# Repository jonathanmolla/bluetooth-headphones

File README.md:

# Bluetooth Headphones

Custom Bluetooth headphone electronics by **Jonathan Molla**, bringing together stereo audio circuit design, PCB layout, battery charging, STM32 controller configuration, and LTspice simulation.

## Project at a glance

| Area | Implementation in this repository |
| --- | --- |
| Bluetooth audio | Microchip BM83 module in the KiCad audio schematic |
| Headphone amplifier | TI TPA6130A2, with AC-coupled analog inputs |
| Controller | STM32U031C8T6 configuration and MCU/button schematic |
| Charging | MCP73833 circuit on a separate power PCB |
| Regulation | TPS7A2030PDBVR, fixed 3.0 V regulator |
| Design tools | KiCad, STM32CubeMX, LTspice |
| Simulation scope | Simplified analog coupling and voltage-gain models |

## Explore the project

| What you want to see | Where to find it |
| --- | --- |
| **PCB layouts and editable board files** | [Main audio PCB](hardware/main/#main-audio-pcb) · [Charging and power PCB](hardware/power/#charging-and-power-pcb) |
| **Schematics** | [Audio, controller, and charging circuit diagrams](docs/schematics/) |
| **Board images** | [Main audio and power board previews](docs/images/) |
| **Circuit design and component choices** | [Architecture and design decisions](docs/design.md) |
| **STM32 configuration** | [Controller pin and peripheral configuration](firmware/) |
| **Audio simulation** | [LTspice circuit, models, and run instructions](simulation/) |
| **Component lists** | [Main audio board BOM](hardware/main/bom.csv) · [Power board BOM](hardware/power/bom.csv) |
| **Engineering checks** | [Schematic and PCB check results](docs/validation.md) |
| **Opening the design files** | [Software and setup guide](docs/getting-started.md) |
| **Design deliverables** | [Project file guide](docs/roadmap.md) |

## System architecture

```mermaid
flowchart LR
    BT[Bluetooth source] --> BM[BM83 module]
    BM --> AC[AC coupling]
    AC --> AMP[TPA6130A2 amplifier]
    AMP --> HP[Left and right headphone drivers]
    USB[USB power input] --> CHG[MCP73833 charging circuit]
    CHG <--> BAT[Single-cell battery]
    BAT --> RAIL[VBAT rail]
    RAIL --> BM
    RAIL --> AMP
    RAIL --> LDO[TPS7A20 3.0 V regulator]
    LDO --> MCU[STM32U031 controller]
    BTN[Buttons] --> MCU
    MCU -. control interfaces .-> BM
    MCU -. I2C control .-> AMP
```

This is an architectural overview. Exact connections and component values are defined by the native schematics. The main/audio board and charging/power board are separate KiCad projects.

## Engineering highlights

- Hierarchical schematic organization for audio and MCU controls.
- A separate charging and regulation PCB.
- Project-local symbols and footprints alongside the native KiCad files.
- Stereo AC-coupling analysis with parameterized input resistance, gain, and driver loads.
- STM32 pin and peripheral configuration captured in a reproducible `.ioc` file.
- Recorded KiCad electrical and design-rule checks with a structured measurement procedure.

## Repository layout

```text
hardware/
  main/          Main audio PCB, audio and controller schematics, local libraries
  power/         Charging and power PCB, schematic and local libraries
firmware/        STM32CubeMX controller configuration
simulation/      LTspice audio circuit, symbols, models and instructions
docs/
  images/        PCB layout previews
  schematics/    Browser-readable schematic exports
  checks/        Recorded KiCad design checks
```

## Author and references

Project owner: [Jonathan Molla](https://github.com/jonathanmolla).

See [references and third-party materials](docs/references.md) for component sources and [reuse information](NOTICE.md) before reusing the files.

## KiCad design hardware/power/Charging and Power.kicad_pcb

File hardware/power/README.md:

# Charging and power board

This board contains the USB power input, MCP73833 battery-charging circuit, and TPS7A2030PDBVR 3.0 V regulator.

## Charging and power PCB

**Editable board layout:** [Charging and Power.kicad_pcb](Charging%20and%20Power.kicad_pcb)

**Open the complete KiCad project:** [Charging and Power.kicad_pro](Charging%20and%20Power.kicad_pro)

**View the layout in your browser:** [Charging and power PCB preview](../../docs/images/power-board.svg)

## Schematic and component list

| File | Contents |
| --- | --- |
| [Power schematic](Charging%20and%20Power.kicad_sch) | Charging, regulation, indicators and board connections |
| [Component list](bom.csv) | Schematic references, values, footprints and datasheet links |

[View the power schematic](../../docs/schematics/power/Charging%20and%20Power.svg) · [Open the main audio board](../main/)

## Library files

`MCP73833-AMI_UN.pretty/` and `TPS7A2030PDBVR.pretty/` contain the local charger and regulator CAD assets. Keep these folders and both library tables beside the project when downloading it.

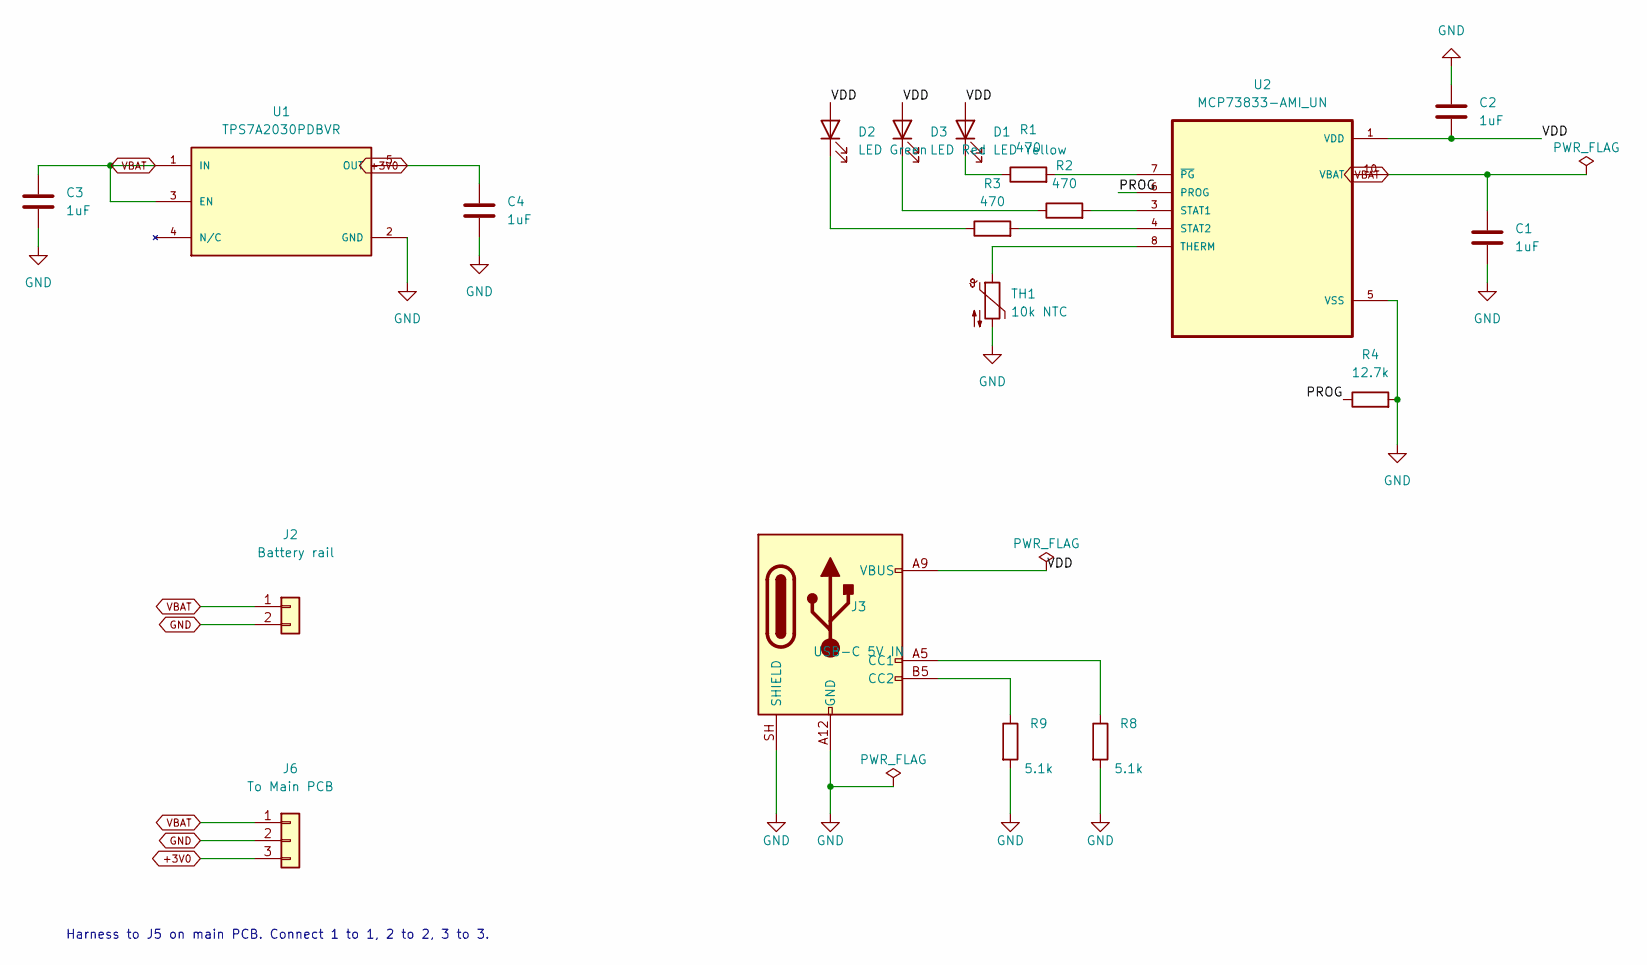
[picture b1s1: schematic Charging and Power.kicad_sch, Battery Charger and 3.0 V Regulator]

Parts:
C1, C2, C3, C4: 1uF; C_0805_2012Metric; MPN GRM219R71E105KA88D
D1: LED Yellow; LED_0805_2012Metric; MPN AP2012SYC
D2: LED Green; LED_0805_2012Metric; MPN AP2012SGC
D3: LED Red; LED_0805_2012Metric; MPN APT2012SURCK
J2: Battery rail; JST_PH_B2B-PH-K_1x02_P2.00mm_Vertical; MPN B2B-PH-K-S(LF)(SN)
J3: USB-C 5V IN; USB_C_Receptacle_GCT_USB4125-xx-x_6P_TopMnt_Horizontal; MPN USB4125-GF-A
J6: To Main PCB; JST_PH_B3B-PH-K_1x03_P2.00mm_Vertical; MPN B3B-PH-K-S(LF)(SN)
R1, R2, R3: 470; R_0805_2012Metric; MPN ERJ-6ENF4700V
R4: 12.7k; R_0603_1608Metric; MPN RC0603FR-0712K7L
R8, R9: 5.1k; R_0805_2012Metric; MPN RC0805FR-075K1L
TH1: 10k NTC; SolderWire-0.1sqmm_1x02_P3.6mm_D0.4mm_OD1mm; MPN B57861S0103F040
U1: TPS7A2030PDBVR; SOT95P280X145-5N; PARTREV H
U2: MCP73833-AMI_UN; SOP50P490X110-10N

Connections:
+3V0: C4.1, J6.3, U1.5 (OUT)
/PROG: R4.1, U2.6 (PROG)
GND: C1.2, C2.1, C3.2, C4.2, J2.2, J3.A12 (GND), J3.B12 (GND), J3.SH (SHIELD), J6.2, R4.2, R8.2, R9.2, TH1.2, U1.2 (GND), U2.5 (VSS)
unnamed: D1.1 (K), R1.1
unnamed: D2.1 (K), R3.1
unnamed: D3.1 (K), R2.1
unnamed: J3.A5 (CC1), R8.1
unnamed: J3.B5 (CC2), R9.1
unnamed: R2.2, U2.3 (STAT1)
unnamed: R3.2, U2.4 (STAT2)
unnamed: TH1.1, U2.8 (THERM)
unnamed: R1.2, U2.7 (~PG)
VBAT: C1.1, C3.1, J2.1, J6.1, U1.1 (IN), U1.3 (EN), U2.9 (VBAT), U2.10 (VBAT)
VDD: C2.2, D1.2 (A), D2.2 (A), D3.2 (A), J3.A9 (VBUS), J3.B9 (VBUS), U2.1 (VDD), U2.2 (VDD)

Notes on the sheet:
Harness to J5 on main PCB. Connect 1 to 1, 2 to 2, 3 to 3.

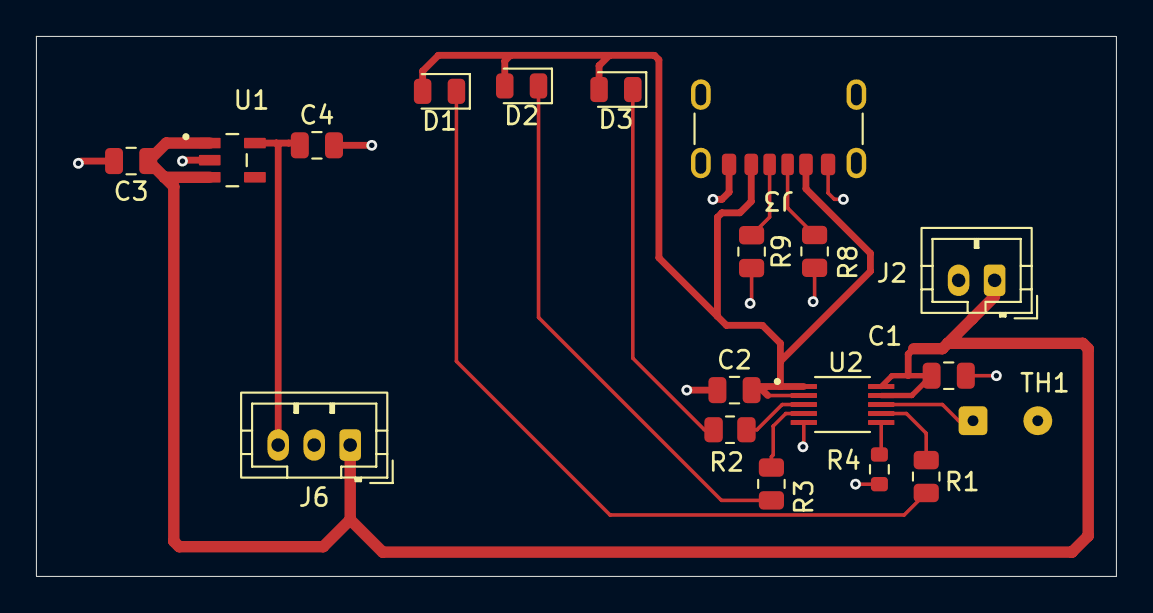
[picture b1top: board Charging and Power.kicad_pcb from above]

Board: 2 copper layers, 60.0 x 30.0 mm, 19 parts (0 on the bottom side), 14 nets.

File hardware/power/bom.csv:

Reference,Value,Footprint,Datasheet,Status
C1,1uF,Capacitor_SMD:C_0805_2012Metric,,Schematic-derived; verify before purchasing
C2,1uF,Capacitor_SMD:C_0805_2012Metric,,Schematic-derived; verify before purchasing
C3,1uF,Capacitor_SMD:C_0805_2012Metric,,Schematic-derived; verify before purchasing
C4,1uF,Capacitor_SMD:C_0805_2012Metric,,Schematic-derived; verify before purchasing
D1,LED Yellow,LED_SMD:LED_0805_2012Metric,,Schematic-derived; verify before purchasing
D2,LED Green,LED_SMD:LED_0805_2012Metric,,Schematic-derived; verify before purchasing
D3,LED Red,LED_SMD:LED_0805_2012Metric,,Schematic-derived; verify before purchasing
J2,Battery rail,Connector_JST:JST_PH_B2B-PH-K_1x02_P2.00mm_Vertical,,Schematic-derived; verify before purchasing
J3,USB-C 5V IN,Connector_USB:USB_C_Receptacle_GCT_USB4125-xx-x_6P_TopMnt_Horizontal,,Schematic-derived; verify before purchasing
J6,To Main PCB,Connector_JST:JST_PH_B3B-PH-K_1x03_P2.00mm_Vertical,,Schematic-derived; verify before purchasing
R1,470,Resistor_SMD:R_0805_2012Metric,,Schematic-derived; verify before purchasing
R2,470,Resistor_SMD:R_0805_2012Metric,,Schematic-derived; verify before purchasing
R3,470,Resistor_SMD:R_0805_2012Metric,,Schematic-derived; verify before purchasing
R4,12.7k,Resistor_SMD:R_0603_1608Metric,,Schematic-derived; verify before purchasing
R8,5.1k,Resistor_SMD:R_0805_2012Metric,,Schematic-derived; verify before purchasing
R9,5.1k,Resistor_SMD:R_0805_2012Metric,,Schematic-derived; verify before purchasing
TH1,10k NTC,Connector_Wire:SolderWire-0.1sqmm_1x02_P3.6mm_D0.4mm_OD1mm,,Schematic-derived; verify before purchasing
U1,TPS7A2030PDBVR,TPS7A2030PDBVR:SOT95P280X145-5N,,Schematic-derived; verify before purchasing
U2,MCP73833-AMI_UN,MCP73833-AMI_UN:SOP50P490X110-10N,,Schematic-derived; verify before purchasing

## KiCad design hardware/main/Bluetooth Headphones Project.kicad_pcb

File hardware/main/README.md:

# Main audio board

This board brings together BM83 Bluetooth audio, the TPA6130A2 headphone amplifier, and the STM32 controller and button circuitry.

## Main audio PCB

**Editable board layout:** [Bluetooth Headphones Project.kicad_pcb](Bluetooth%20Headphones%20Project.kicad_pcb)

**Open the complete KiCad project:** [Bluetooth Headphones Project.kicad_pro](Bluetooth%20Headphones%20Project.kicad_pro)

**View the layout in your browser:** [Main audio PCB preview](../../docs/images/main-board.svg)

## Schematics and component list

| File | Contents |
| --- | --- |
| [Root schematic](Bluetooth%20Headphones%20Project.kicad_sch) | Project hierarchy linking the audio and controller sheets |
| [Audio schematic](Bluetooth_Audio.kicad_sch) | BM83 module, AC coupling, TPA6130A2 amplifier and headphone outputs |
| [Controller schematic](MCU_Buttons.kicad_sch) | STM32 controller and button connections |
| [Component list](bom.csv) | Schematic references, values, footprints and datasheet links |

[View all schematic previews](../../docs/schematics/) · [Open the separate charging and power board](../power/)

## Library files

`Project_Audio.pretty/` and `STM32.pretty/` contain project-local footprints. The `.kicad_sym` files contain project-local symbols. Keep these folders and both library tables beside the project when downloading it.

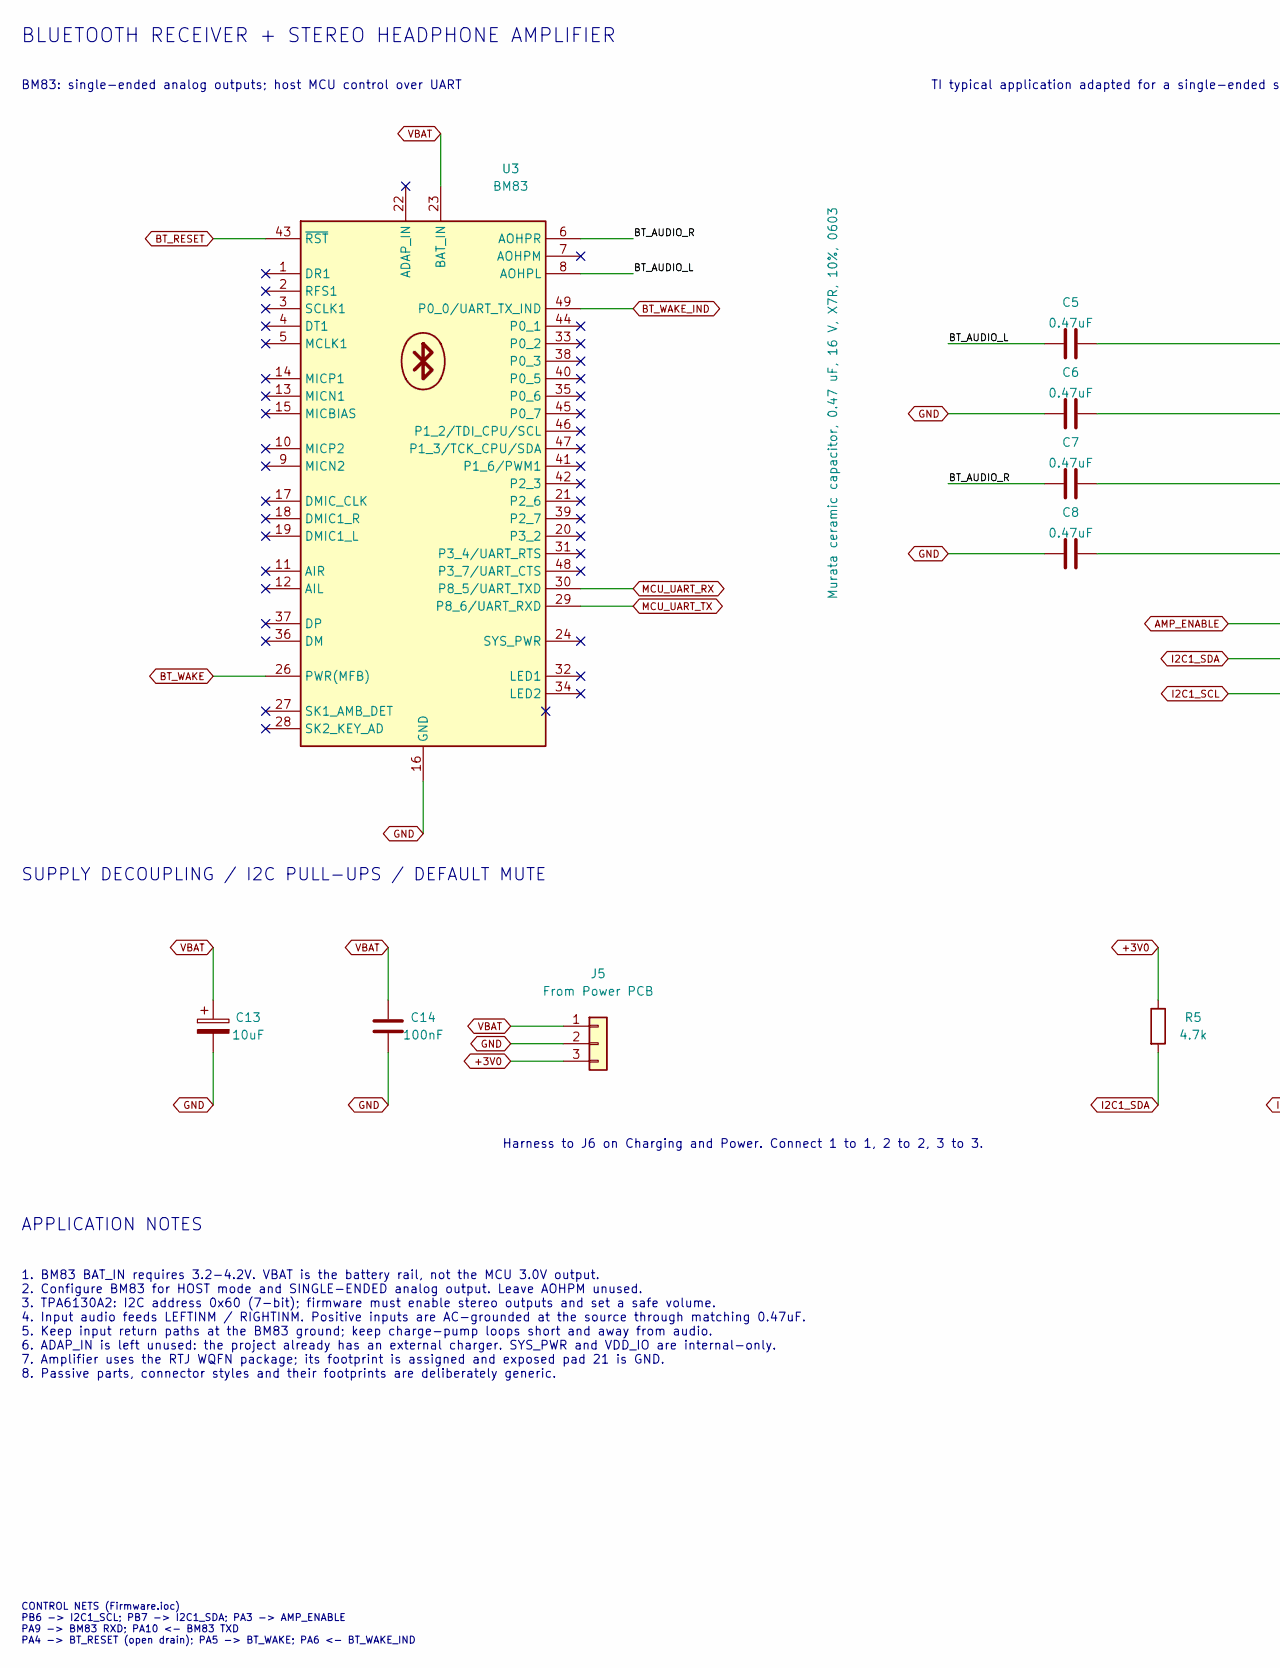
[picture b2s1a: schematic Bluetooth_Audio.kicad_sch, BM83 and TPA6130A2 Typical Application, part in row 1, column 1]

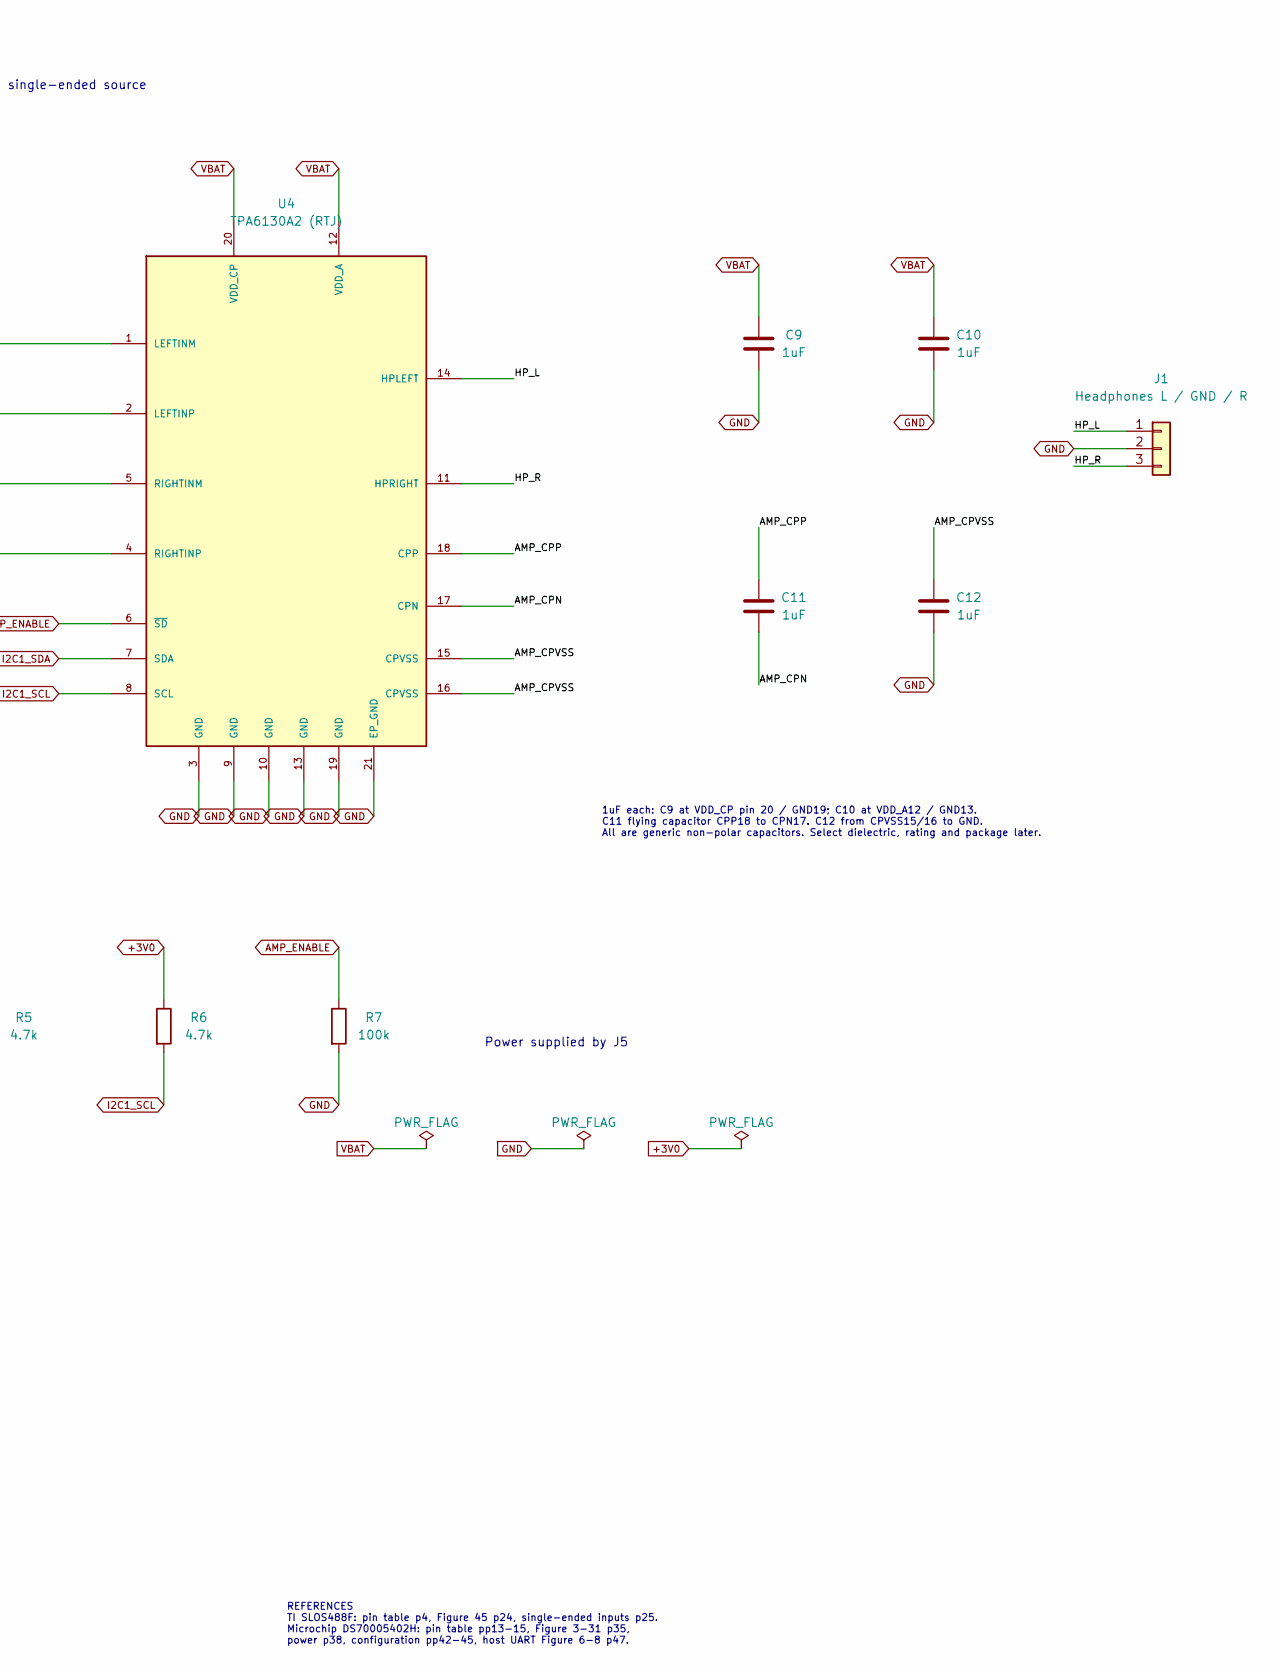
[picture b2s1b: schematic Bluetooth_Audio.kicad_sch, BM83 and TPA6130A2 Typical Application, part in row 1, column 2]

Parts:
C5, C6, C7, C8: 0.47uF; C_0603_1608Metric; MPN GRM188R71C474KA88D
C9, C10, C11, C12: 1uF; C_0805_2012Metric; MPN GRM219R71E105KA88D
C13: 10uF; CP_Elec_4x5.8; MPN EEE-FN1C100R
C14: 100nF; C_0603_1608Metric; MPN GRM188R72A104KA35J
J1: Headphones L / GND / R; PinHeader_1x03_P2.54mm_Vertical; MPN TSW-103-07-G-S
J5: From Power PCB; JST_PH_B3B-PH-K_1x03_P2.00mm_Vertical; MPN B3B-PH-K-S(LF)(SN)
R5, R6: 4.7k; R_0603_1608Metric; MPN RC0603FR-074K7L
R7: 100k; R_0603_1608Metric; MPN RC0603FR-07100KL
U3: BM83; Microchip_BM83
U4: TPA6130A2 (RTJ); TPA6130A2_RTJ_4x4mm_P0.5mm_EP2.7x2.7mm

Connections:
+3V0: J5.3, R5.1, R6.1; also elsewhere on the board
/Bluetooth_and_Audio/AMP_CPN: C11.2, U4.17 (CPN)
/Bluetooth_and_Audio/AMP_CPP: C11.1, U4.18 (CPP)
/Bluetooth_and_Audio/AMP_CPVSS: C12.1, U4.15 (CPVSS), U4.16 (CPVSS)
/Bluetooth_and_Audio/BT_AUDIO_L: C5.2, U3.8 (AOHPL)
/Bluetooth_and_Audio/BT_AUDIO_R: C7.2, U3.6 (AOHPR)
/Bluetooth_and_Audio/HP_L: J1.1, U4.14 (HPLEFT)
/Bluetooth_and_Audio/HP_R: J1.3, U4.11 (HPRIGHT)
AMP_ENABLE: R7.1, U4.6 (~SD); also elsewhere on the board
BT_RESET: U3.43 (~RST); also elsewhere on the board
BT_WAKE: U3.26 (PWR(MFB)); also elsewhere on the board
BT_WAKE_IND: U3.49 (P0_0/UART_TX_IND); also elsewhere on the board
GND: C6.2, C8.2, C9.2, C10.2, C12.2, C13.2, C14.2, J1.2, J5.2, R7.2, U3.16 (GND), U3.50 (GND), U3.56 (GND), U3.57 (GND), U4.3 (GND), U4.9 (GND), U4.10 (GND), U4.13 (GND), U4.19 (GND), U4.21 (EP_GND); also elsewhere on the board
I2C1_SCL: R6.2, U4.8 (SCL); also elsewhere on the board
I2C1_SDA: R5.2, U4.7 (SDA); also elsewhere on the board
MCU_UART_RX: U3.30 (P8_5/UART_TXD); also elsewhere on the board
MCU_UART_TX: U3.29 (P8_6/UART_RXD); also elsewhere on the board
unnamed: C5.1, U4.1 (LEFTINM)
unnamed: C6.1, U4.2 (LEFTINP)
unnamed: C7.1, U4.5 (RIGHTINM)
unnamed: C8.1, U4.4 (RIGHTINP)
VBAT: C9.1, C10.1, C13.1, C14.1, J5.1, U3.23 (BAT_IN), U4.12 (VDD_A), U4.20 (VDD_CP); also elsewhere on the board

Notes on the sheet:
SUPPLY DECOUPLING / I2C PULL-UPS / DEFAULT MUTE
REFERENCES TI SLOS488F: pin table p4, Figure 45 p24, single-ended inputs p25. Microchip DS70005402H: pin table pp13-15, Figure 3-31 p35, power p38, configuration pp42-45, host UART Figure 6-8 p47.
1uF each: C9 at VDD_CP pin 20 / GND19; C10 at VDD_A12 / GND13. C11 flying capacitor CPP18 to CPN17. C12 from CPVSS15/16 to GND. All are generic non-polar capacitors. Select dielectric, rating and package later.
CONTROL NETS (Firmware.ioc) PB6 -> I2C1_SCL; PB7 -> I2C1_SDA; PA3 -> AMP_ENABLE PA9 -> BM83 RXD; PA10 <- BM83 TXD PA4 -> BT_RESET (open drain); PA5 -> BT_WAKE; PA6 <- BT_WAKE_IND
1. BM83 BAT_IN requires 3.2-4.2V. VBAT is the battery rail, not the MCU 3.0V output. 2. Configure BM83 for HOST mode and SINGLE-ENDED analog output. Leave AOHPM unused. 3. TPA6130A2: I2C address 0x60 (7-bit); firmware must enable stereo outputs and set a safe volume. 4. Input audio feeds LEFTINM / 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
Harness to J6 on Charging and Power. Connect 1 to 1, 2 to 2, 3 to 3.
APPLICATION NOTES
TI typical application adapted for a single-ended source
BLUETOOTH RECEIVER + STEREO HEADPHONE AMPLIFIER
BM83: single-ended analog outputs; host MCU control over UART
Power supplied by J5

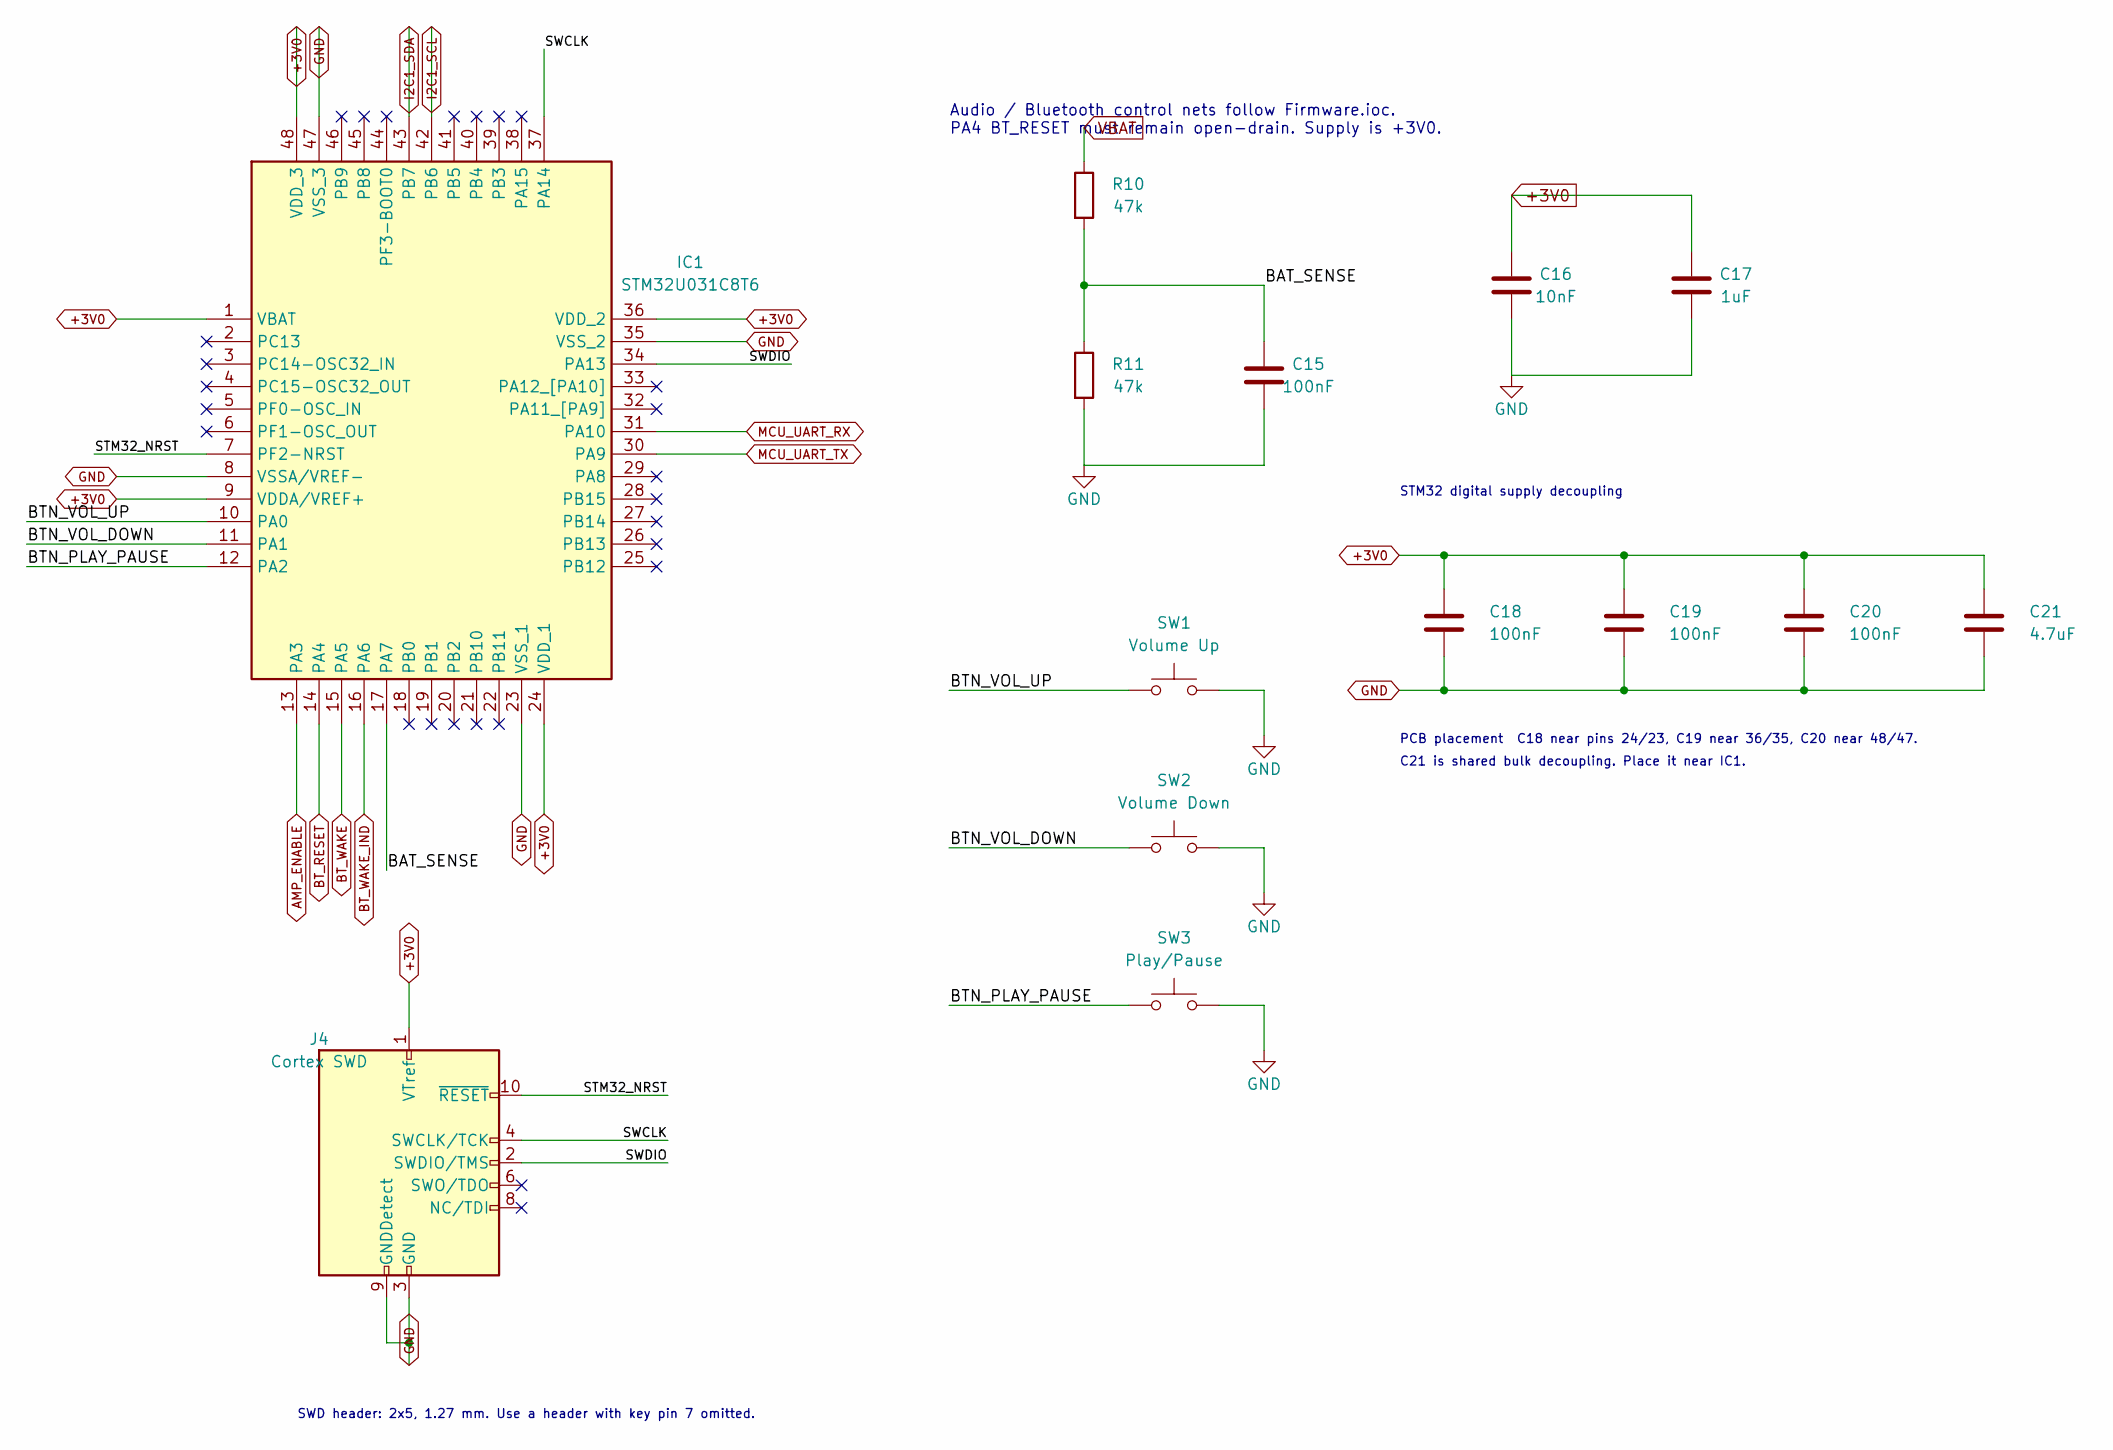
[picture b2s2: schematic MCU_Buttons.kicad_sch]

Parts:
C15: 100nF; C_0603_1608Metric; MPN GRM188R72A104KA35J
C16: 10nF; C_0603_1608Metric; MPN CC0603KRX7R9BB103
C17: 1uF; C_0805_2012Metric; MPN GRM219R71E105KA88D
C18, C19, C20: 100nF; C_0603_1608Metric
C21: 4.7uF; C_0805_2012Metric
IC1: STM32U031C8T6; QFP50P900X900X160-48N; Manufacturer_Part_Number STM32U031C8T6; Mouser Part Number 511-STM32U031C8T6
J4: Cortex SWD; PinHeader_2x05_P1.27mm_Vertical
R10, R11: 47k; R_0603_1608Metric; MPN RC0603FR-0747KL
SW1: Volume Up; SW_TH_Tactile_Omron_B3F-100x; MPN B3F-1002-G
SW2: Volume Down; SW_TH_Tactile_Omron_B3F-100x; MPN B3F-1002-G
SW3: Play/Pause; SW_TH_Tactile_Omron_B3F-100x; MPN B3F-1002-G

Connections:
+3V0: C16.1, C17.1, C18.1, C19.1, C20.1, C21.1, IC1.1 (VBAT), IC1.9 (VDDA/VREF+), IC1.24 (VDD_1), IC1.36 (VDD_2), IC1.48 (VDD_3), J4.1 (VTref); also elsewhere on the board
/MCU_and_Buttons/BAT_SENSE: C15.1, IC1.17 (PA7), R10.2, R11.1
/MCU_and_Buttons/BTN_PLAY_PAUSE: IC1.12 (PA2), SW3.1
/MCU_and_Buttons/BTN_VOL_DOWN: IC1.11 (PA1), SW2.1
/MCU_and_Buttons/BTN_VOL_UP: IC1.10 (PA0), SW1.1
/MCU_and_Buttons/STM32_NRST: IC1.7 (PF2-NRST), J4.10 (~RESET)
/MCU_and_Buttons/SWCLK: IC1.37 (PA14), J4.4 (SWCLK/TCK)
/MCU_and_Buttons/SWDIO: IC1.34 (PA13), J4.2 (SWDIO/TMS)
AMP_ENABLE: IC1.13 (PA3); also elsewhere on the board
BT_RESET: IC1.14 (PA4); also elsewhere on the board
BT_WAKE: IC1.15 (PA5); also elsewhere on the board
BT_WAKE_IND: IC1.16 (PA6); also elsewhere on the board
GND: C15.2, C16.2, C17.2, C18.2, C19.2, C20.2, C21.2, IC1.8 (VSSA/VREF-), IC1.23 (VSS_1), IC1.35 (VSS_2), IC1.47 (VSS_3), J4.3 (GND), J4.5 (GND), J4.9 (GNDDetect), R11.2, SW1.2, SW2.2, SW3.2; also elsewhere on the board
I2C1_SCL: IC1.42 (PB6); also elsewhere on the board
I2C1_SDA: IC1.43 (PB7); also elsewhere on the board
MCU_UART_RX: IC1.31 (PA10); also elsewhere on the board
MCU_UART_TX: IC1.30 (PA9); also elsewhere on the board
VBAT: R10.1; also elsewhere on the board

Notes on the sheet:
C21 is shared bulk decoupling. Place it near IC1.
Audio / Bluetooth control nets follow Firmware.ioc. PA4 BT_RESET must remain open-drain. Supply is +3V0.
STM32 digital supply decoupling
SWD header: 2x5, 1.27 mm. Use a header with key pin 7 omitted.
PCB placement C18 near pins 24/23, C19 near 36/35, C20 near 48/47.

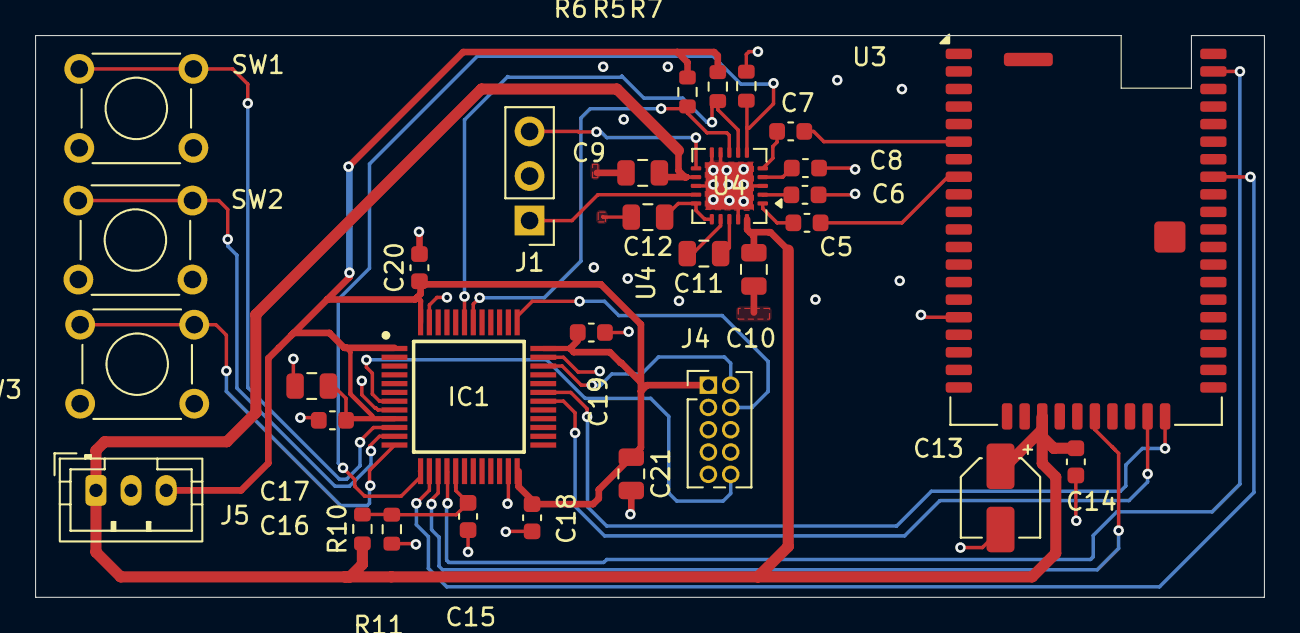
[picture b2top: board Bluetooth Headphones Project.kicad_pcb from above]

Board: 4 copper layers, 70.0 x 32.0 mm, 31 parts (0 on the bottom side), 29 nets.

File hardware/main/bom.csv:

Reference,Value,Footprint,Datasheet,Status
C15,100nF,Capacitor_SMD:C_0603_1608Metric,,Schematic-derived; verify before purchasing
C16,10nF,Capacitor_SMD:C_0603_1608Metric,,Schematic-derived; verify before purchasing
C17,1uF,Capacitor_SMD:C_0805_2012Metric,,Schematic-derived; verify before purchasing
C18,100nF,Capacitor_SMD:C_0603_1608Metric,,Schematic-derived; verify before purchasing
C19,100nF,Capacitor_SMD:C_0603_1608Metric,,Schematic-derived; verify before purchasing
C20,100nF,Capacitor_SMD:C_0603_1608Metric,,Schematic-derived; verify before purchasing
C21,4.7uF,Capacitor_SMD:C_0805_2012Metric,,Schematic-derived; verify before purchasing
IC1,STM32U031C8T6,STM32:QFP50P900X900X160-48N,https://www.st.com/resource/en/datasheet/stm32u031f4.pdf,Schematic-derived; verify before purchasing
J4,Cortex SWD,Connector_PinHeader_1.27mm:PinHeader_2x05_P1.27mm_Vertical,,Schematic-derived; verify before purchasing
R10,47k,Resistor_SMD:R_0603_1608Metric,,Schematic-derived; verify before purchasing
R11,47k,Resistor_SMD:R_0603_1608Metric,,Schematic-derived; verify before purchasing
SW1,Volume Up,Button_Switch_THT:SW_TH_Tactile_Omron_B3F-100x,,Schematic-derived; verify before purchasing
SW2,Volume Down,Button_Switch_THT:SW_TH_Tactile_Omron_B3F-100x,,Schematic-derived; verify before purchasing
SW3,Play/Pause,Button_Switch_THT:SW_TH_Tactile_Omron_B3F-100x,,Schematic-derived; verify before purchasing
C5,0.47uF,Capacitor_SMD:C_0603_1608Metric,,Schematic-derived; verify before purchasing
C6,0.47uF,Capacitor_SMD:C_0603_1608Metric,,Schematic-derived; verify before purchasing
C7,0.47uF,Capacitor_SMD:C_0603_1608Metric,,Schematic-derived; verify before purchasing
C8,0.47uF,Capacitor_SMD:C_0603_1608Metric,,Schematic-derived; verify before purchasing
C9,1uF,Capacitor_SMD:C_0805_2012Metric,,Schematic-derived; verify before purchasing
C10,1uF,Capacitor_SMD:C_0805_2012Metric,,Schematic-derived; verify before purchasing
C11,1uF,Capacitor_SMD:C_0805_2012Metric,,Schematic-derived; verify before purchasing
C12,1uF,Capacitor_SMD:C_0805_2012Metric,,Schematic-derived; verify before purchasing
C13,10uF,Capacitor_SMD:CP_Elec_4x5.8,,Schematic-derived; verify before purchasing
C14,100nF,Capacitor_SMD:C_0603_1608Metric,,Schematic-derived; verify before purchasing
J1,Headphones L / GND / R,Connector_PinHeader_2.54mm:PinHeader_1x03_P2.54mm_Vertical,,Schematic-derived; verify before purchasing
J5,From Power PCB,Connector_JST:JST_PH_B3B-PH-K_1x03_P2.00mm_Vertical,,Schematic-derived; verify before purchasing
R5,4.7k,Resistor_SMD:R_0603_1608Metric,,Schematic-derived; verify before purchasing
R6,4.7k,Resistor_SMD:R_0603_1608Metric,,Schematic-derived; verify before purchasing
R7,100k,Resistor_SMD:R_0603_1608Metric,,Schematic-derived; verify before purchasing
U3,BM83,RF_Module:Microchip_BM83,,Schematic-derived; verify before purchasing
U4,TPA6130A2 (RTJ),Project_Audio:TPA6130A2_RTJ_4x4mm_P0.5mm_EP2.7x2.7mm,,Schematic-derived; verify before purchasing

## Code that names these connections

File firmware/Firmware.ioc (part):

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Mcu.Name=STM32U031C8Tx
Mcu.Package=LQFP48
Mcu.UserName=STM32U031C8Tx
PA0.GPIOParameters=GPIO_PuPd,GPIO_Label
PA0.GPIO_Label=BTN_VOL_UP
PA0.GPIO_PuPd=GPIO_PULLUP
PA0.Signal=GPIO_Input
PA1.GPIOParameters=GPIO_PuPd,GPIO_Label
PA1.GPIO_Label=BTN_VOL_DOWN
PA1.GPIO_PuPd=GPIO_PULLUP
PA1.Signal=GPIO_Input
PA10.Signal=USART1_RX
PA13\ (SWDIO).Mode=Serial_Wire
PA13\ (SWDIO).Signal=DEBUG_JTMS-SWDIO
PA14\ (SWCLK).Mode=Serial_Wire
PA14\ (SWCLK).Signal=DEBUG_JTCK-SWCLK
PA2.GPIOParameters=GPIO_PuPd,GPIO_Label
PA2.GPIO_Label=BTN_PLAY_PAUSE
PA2.GPIO_PuPd=GPIO_PULLUP
PA2.Signal=GPIO_Input
PA3.GPIOParameters=GPIO_Label
PA3.GPIO_Label=AMP_ENABLE
PA3.Signal=GPIO_Output
PA4.GPIOParameters=PinState,GPIO_PuPd,GPIO_Label,GPIO_ModeDefaultOutputPP
PA4.GPIO_Label=BT_RESET
PA4.GPIO_ModeDefaultOutputPP=GPIO_MODE_OUTPUT_OD
PA4.GPIO_PuPd=GPIO_NOPULL
PA4.PinState=GPIO_PIN_SET
PA4.Signal=GPIO_Output
PA5.GPIOParameters=GPIO_Label
PA5.GPIO_Label=BT_WAKE
PA5.Signal=GPIO_Output
PA6.GPIOParameters=GPIO_Label
PA6.GPIO_Label=BT_WAKE_IND
PA6.Signal=GPIO_Input
PA7.GPIOParameters=GPIO_Label
PA7.GPIO_Label=BAT_SENSE
PA7.Mode=IN14
PA7.Signal=ADC1_IN14
PA9.Signal=USART1_TX
PB6.Mode=I2C
PB6.Signal=I2C1_SCL
PB7.Mode=I2C
PB7.Signal=I2C1_SDA
RCC.HSE_VALUE=4000000
RCC.SYSCLKFreq_VALUE=16000000
board=custom
